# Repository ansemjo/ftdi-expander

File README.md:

# ftdi-expander

The ftdi-expander is a pretty straightforward circuit board that adds a linear
regulator to 3.3 V, two selection jumpers and a few IDC connectors for commonly
used functions. Except for the availability of the 3.3 V voltage it adds no new
functionality – it simply provides easier connections, so you don't have to mess
with jumper wires every time.

## The FT232H

I love my [Adafruit FT232H](https://www.adafruit.com/product/2264). It is
marketed as a "general purpose USB to ..." adapter. And it turns out it is indeed
very versatile!
This very chip – or its two-channel variant FT2232H – is at the heart of many
different programmers and debuggers.

It has a Python library to toggle GPIOs.  
It can be used to [program AVR chips and Arduinos](https://semjonov.de/docs/tips/arduino/#adafruit-ftdi-ft232h-breakout-board).  
It reads your RTC modules over I2C.  
It flashes your EEPROM with flashrom.  
It is supported by OpenOCD to debug various platforms.  
...

Over time I built myself an assortment of cables to use each function more
conveniently. But this also meant that I couldn't use standard cables .. until now.

## The Expander

See the [schematics](https://raw.githubusercontent.com/ansemjo/ftdi-expander/main/schematics.pdf).

This board plugs into your Adafruit FT232H breakout with two female headers and
adds the following features:

### IC: 3.3 V Linear Regulator + VCC Selection Jumper

Drops the voltage from the 5 V USB VBUS down to 3.3 V. The newer revision of the
Adafruit FT232H with a USB-C receptacle adds a dedicated 3.3 V pin but the older
version which is still found in many shops does not provide that.

At the same time all the output pins of the FT232H are using 3.3 V logic levels
while being *5 V safe*. So all you need to interface with some chips that are
**only** capable of 3.3 V is this additional supply.

The output voltage on the `VCC` pin of all connectors can be selected with a
jumper.

### Jumper: I2C Mode

The documentation to this breakout tells you to connect `D1` and `D2` together
when you want to use I2C. Again, the newer revision of the Adafruit FT232H
brings a simple slider switch to short the pins. But the older revision does
not have this luxury.

Use a jumper to short the pins and "enable" I2C mode.

There's also two optional pullup resistors that can be soldered-on in case your
devices do not bring their own. Use something like 10 kΩ and they should not
interfere with any other actively driven protocols while not in I2C mode.

### Connector: Flash Clip

An 8-pin 2.54mm IDC connector with a pinout that is commonly used for 8-SOIC
flash clips. Can be used e.g. with the [Pomona 5250](https://www.digikey.com/products/en?keywords=501-1311-ND)
in conjuntion with `flashrom` to read and write common EEPROM chips:

```
flashrom -p ft2232_spi:type=232H,port=A,csgpiol=3,divisor=4 -r dump.bin
```

### Connector: AVR ICSP Header

A 6-pin 2.54mm IDC connector with a pinout for AVR programming cables. Can be
used with `avrdude` to rescue your Arduino bootloaders or flash bare Atmel
microcontrollers directly. This method is also a lot faster than bit-banging
with a serial adapter.

```
avrdude -c UM232H -p m328p -U flash:w:firmware.hex:i
```

### Connector: ARM Cortex JTAG

A 10-pin 1.27mm pitch connector that is used on modern ARM Cortex platforms. I
don't have a good guide available but I've used a matching connector on my
[chronovfd](https://github.com/ansemjo/chronovfd) and I was somewhat successful
in getting OpenOCD up and running with the ESP32 module:

```
openocd-esp32 -s /usr/share/openocd-esp32/scripts \
  -f interface/ftdi/um232h.cfg \
  -f board/esp-wroom-32.cfg \
  -c "adapter_khz 1000" \
  ...
```

As I mentioned above, this exact chip is used on other debuggers as well. So if
you need a more generic pinout you can use the ...

### Connector: Labelled Male Header

Electrically, the angled male header at the edge is nothing special at all. It
is almost the exact same pinout as the first six pins on the FT232H itself:
`VCC`, `GND`, `D0`, `D1`, `D2` and `D3`.

The difference is that the VCC pin can be switched between VUSB of 5 V and the
regulated 3.3 V.

Furthermore it adds a handy reference table on the silkscreen so you don't have
to look up pin functions in the documentation anymore.

## License

This project is licensed under a [CERN Open Hardware Licence Version 2 - Permissive](LICENSE) license.

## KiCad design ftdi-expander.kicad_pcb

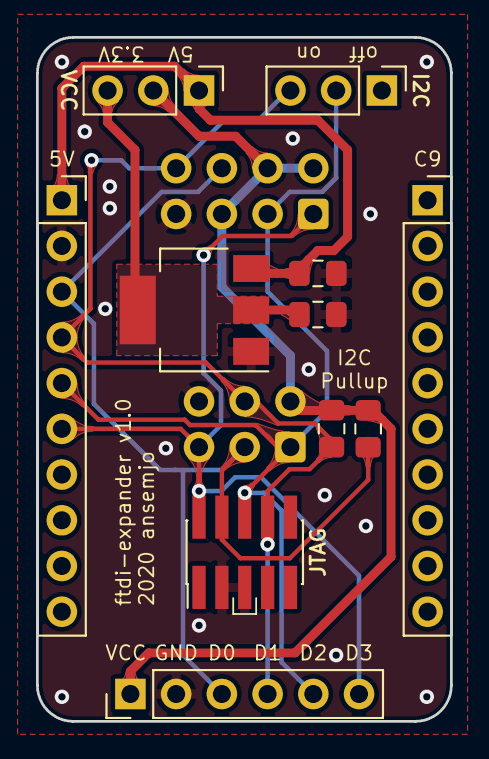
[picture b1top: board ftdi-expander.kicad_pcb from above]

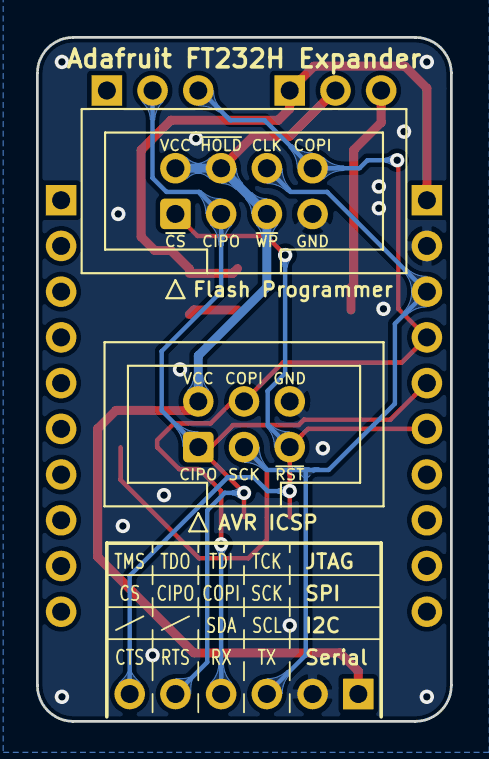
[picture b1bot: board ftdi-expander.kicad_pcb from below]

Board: 2 copper layers, 23.0 x 38.0 mm, 13 parts (2 on the bottom side), 8 nets.

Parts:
C1, C2: 1µF; C_0805_2012Metric_Pad1.15x1.40mm_HandSolder
J1, J2: Conn_01x10; PinSocket_1x10_P2.54mm_Vertical
J3: ARM-JTAG-10; PinHeader_2x05_P1.27mm_Vertical_SMD
J4: IDC 02x04; IDC-Header_2x04_P2.54mm_Vertical
J5: AVR-ISP-6; IDC-Header_2x03_P2.54mm_Vertical
J6: Conn_01x06_Male; PinHeader_1x06_P2.54mm_Vertical
R3, R4: 10kΩ; R_0805_2012Metric_Pad1.15x1.40mm_HandSolder
SW1, SW2: Jumper; PinHeader_1x03_P2.54mm_Vertical
U1: AZ1117EH-3.3TRG1; SOT-223-3_TabPin2

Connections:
+3V3: C2.2, SW1.3, U1.2
+5V: C1.2, J1.1, SW1.1, U1.3
D0: J1.3, J3.4, J4.6, J5.3, J6.3, R4.2
D1: J1.4, J3.8, J4.8, J5.4, J6.4, R3.2, SW2.3
D2: J1.5, J3.6, J4.3, J5.1, J6.5, SW2.2
D3: J1.6, J3.2, J4.1, J5.5, J6.6
GND: C1.1, C2.1, J1.2, J3.3, J3.5, J4.7, J5.6, J6.2, U1.1
VCC: J4.2, J4.4, J4.5, J5.2, J6.1, R3.1, R4.1, SW1.2

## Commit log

2020-09-09 begin tracking work on ft232h expander
2020-09-09 routed version with spdt switches
2020-09-09 replaced switches with jumper headers, tidied up traces, added teardrops
2020-09-09 fixed some drc errors caused by teardrops
2020-09-28 add readme, license, pictures and schematics pdf
2020-09-28 fix schematics link
